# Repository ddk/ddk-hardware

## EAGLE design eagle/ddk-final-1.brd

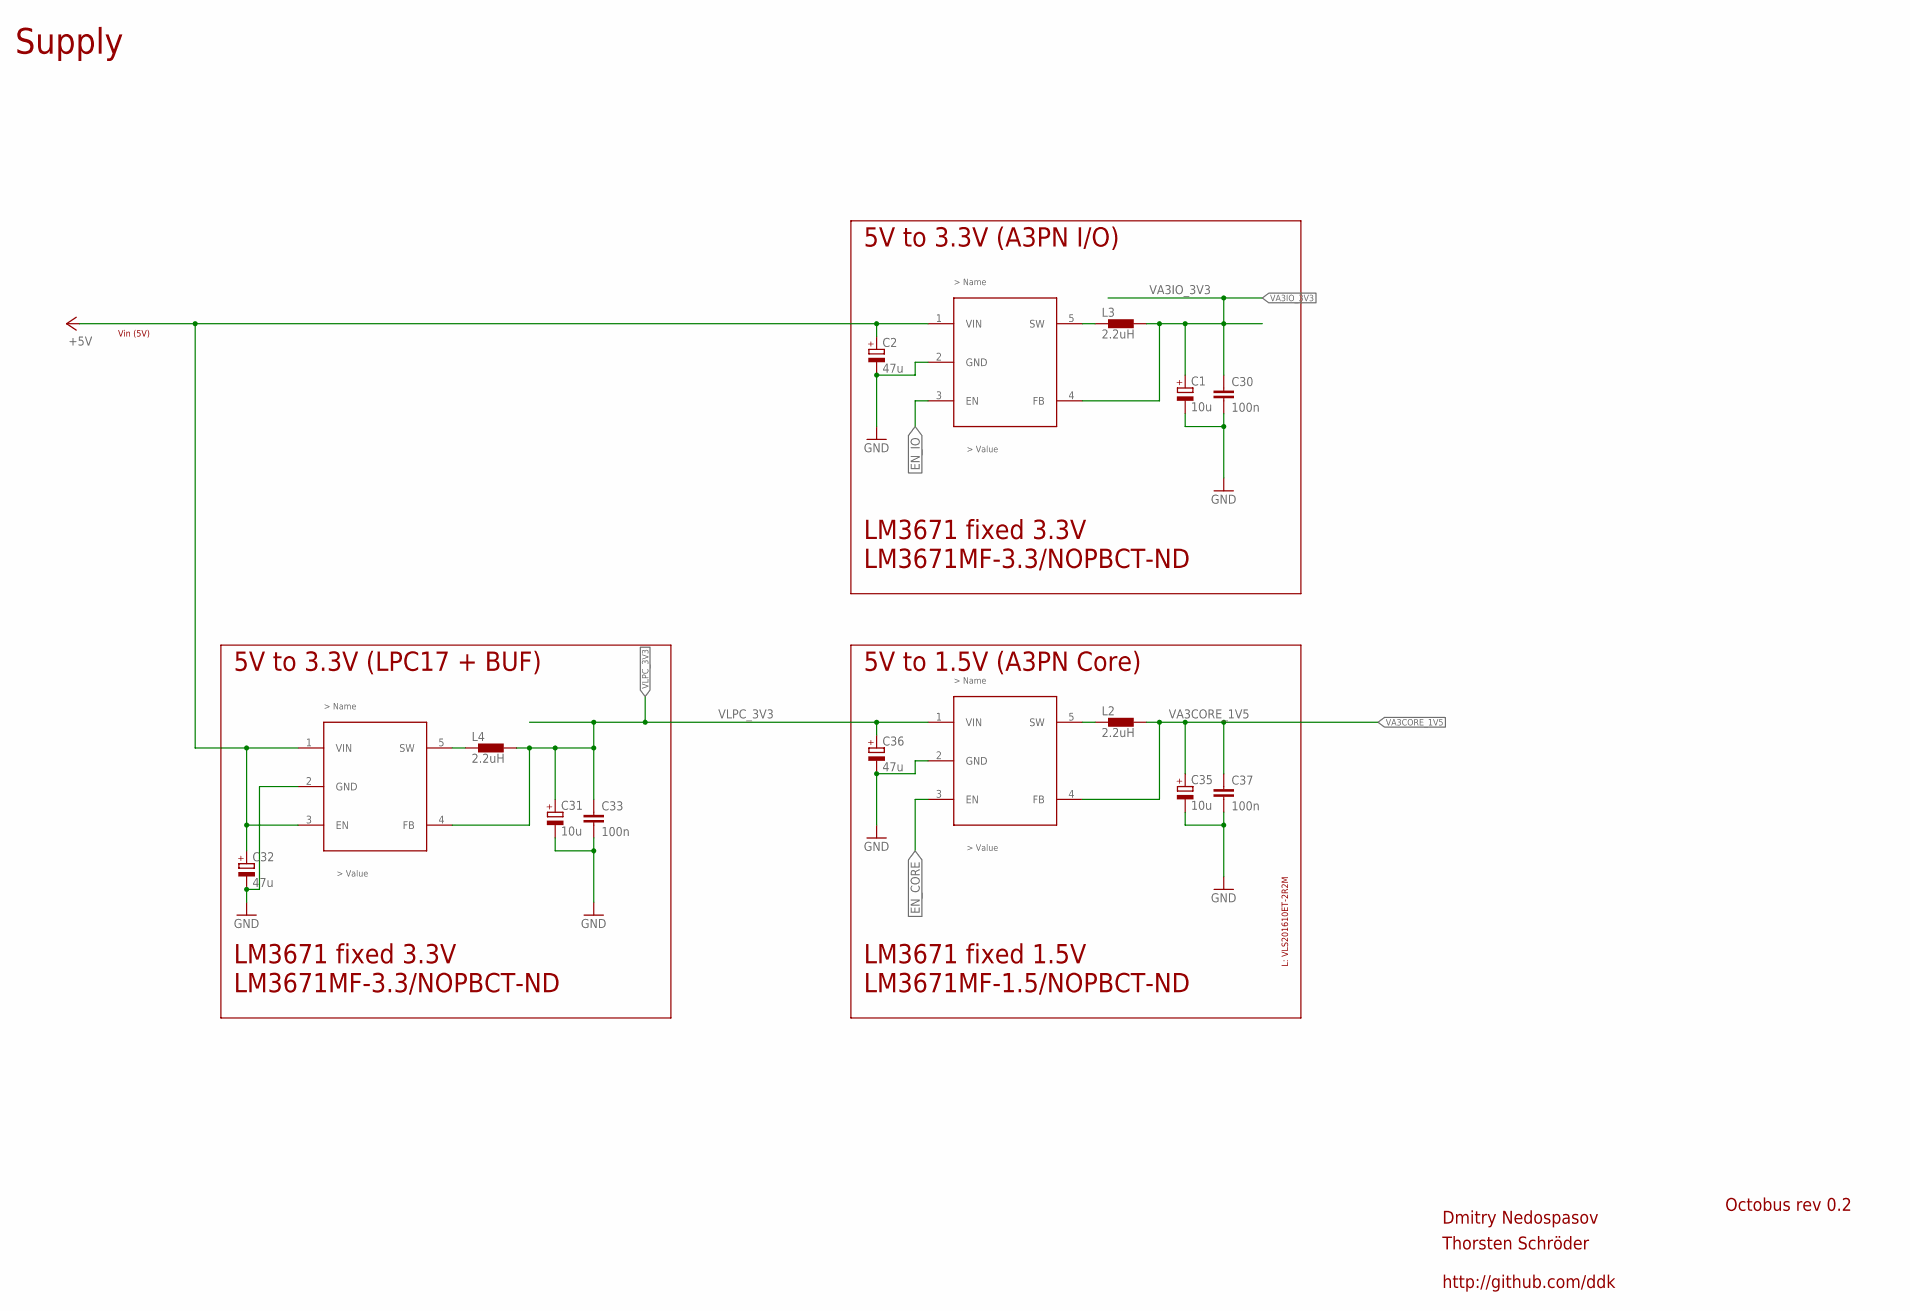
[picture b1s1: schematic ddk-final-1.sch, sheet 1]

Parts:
C1, C31, C35: 10u; CT3216
C2, C32, C36: 47u; CT3216
C30, C33, C37: 100n; C0603K
L2, L3, L4: 2.2uH; VLS_INDUCTOR
LM1: LM3671_3V3IO; SOT23-5L
LM2: LM3671_3V3_LPC; SOT23-5L
LM3671: LM3671_1V5; SOT23-5L

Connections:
+5V: C2.+, C32.+, LM1.1 (VIN), LM2.1 (VIN), LM2.3 (EN); also elsewhere on the board
EN_CORE: LM3671.3 (EN); also elsewhere on the board
EN_IO: LM1.3 (EN); also elsewhere on the board
GND: C1.-, C2.-, C30.2, C31.-, C32.-, C33.2, C35.-, C36.-, C37.2, LM1.2 (GND), LM2.2 (GND), LM3671.2 (GND); also elsewhere on the board
unnamed: L2.P$1 (1), LM3671.5 (SW)
unnamed: L3.P$1 (1), LM1.5 (SW)
unnamed: L4.P$1 (1), LM2.5 (SW)
VA3CORE_1V5: C35.+, C37.1, L2.P$2 (2), LM3671.4 (FB); also elsewhere on the board
VA3IO_3V3: C1.+, C30.1, L3.P$2 (2), LM1.4 (FB); also elsewhere on the board
VLPC_3V3: C31.+, C33.1, C36.+, L4.P$2 (2), LM2.4 (FB), LM3671.1 (VIN); also elsewhere on the board

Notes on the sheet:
Supply
Vin (5V)
5V to 1.5V (A3PN Core)
5V to 3.3V (A3PN I/O)
5V to 3.3V (LPC17 + BUF)
LM3671 fixed 1.5V LM3671MF-1.5/NOPBCT-ND
L: VLS201610ET-2R2M
LM3671 fixed 3.3V LM3671MF-3.3/NOPBCT-ND

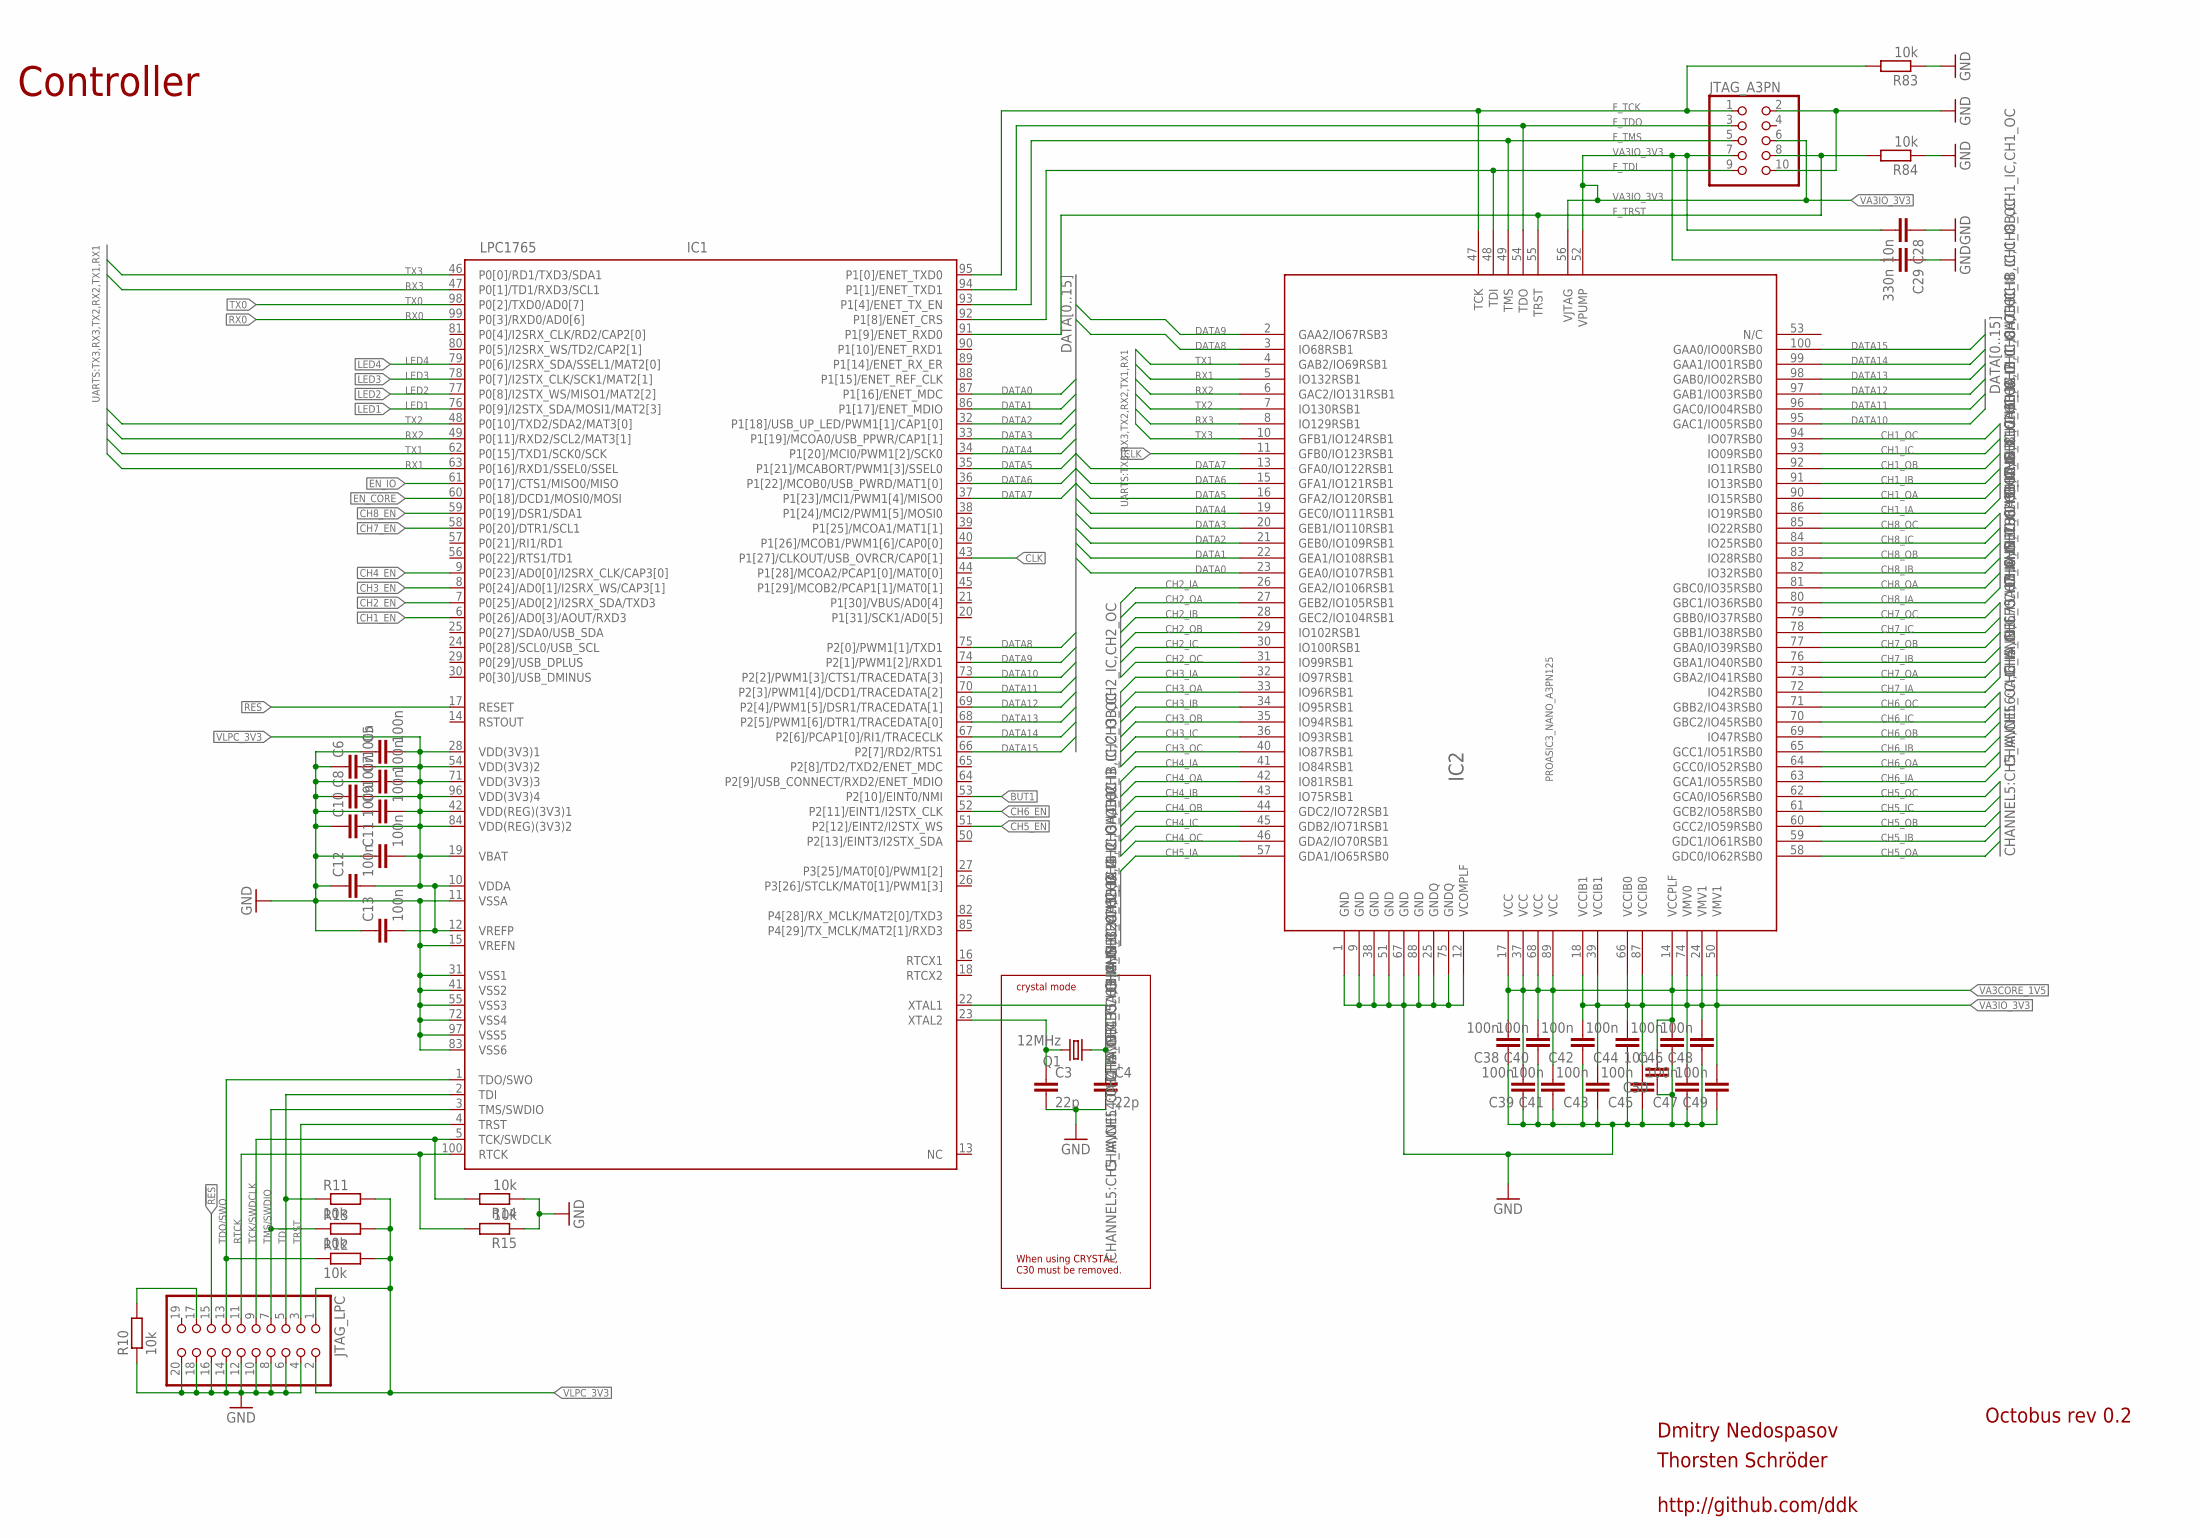
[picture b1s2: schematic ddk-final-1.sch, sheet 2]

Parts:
C3, C4: 22p; C0603K
C5, C6, C7, C8, C9, C10, C11, C12, C13, C38, C39, C40, C41, C42, C43, C44, C45, C46, C47, C48, C49: 100n; C0603K
C28, C50: 10n; C0603K
C29: 330n; C0603K
IC1: LPC1765; LQFP100-14X14
IC2: PROASIC3_NANO_A3PN125; VQFP100
JTAG_A3PN: PINHD-2X05_2.54-SMD; 2X05SMD
JTAG_LPC: PINHD-2X10_2.54-SMD; 2X10SMD
Q1: 12MHz; CTS406
R10, R11, R12, R13, R14, R15, R83, R84: 10k; R0603

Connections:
!RES!: IC1.17 (RESET), JTAG_LPC.15; also elsewhere on the board
BUT1: IC1.53 (P2[10]/EINT0/NMI); also elsewhere on the board
CH1_EN: IC1.6 (P0[26]/AD0[3]/AOUT/RXD3); also elsewhere on the board
CH1_IA: IC2.86 (IO19RSB0); also elsewhere on the board
CH1_IB: IC2.91 (IO13RSB0); also elsewhere on the board
CH1_IC: IC2.93 (IO09RSB0); also elsewhere on the board
CH1_OA: IC2.90 (IO15RSB0); also elsewhere on the board
CH1_OB: IC2.92 (IO11RSB0); also elsewhere on the board
CH1_OC: IC2.94 (IO07RSB0); also elsewhere on the board
CH2_EN: IC1.7 (P0[25]/AD0[2]/I2SRX_SDA/TXD3); also elsewhere on the board
CH2_IA: IC2.26 (GEA2/IO106RSB1); also elsewhere on the board
CH2_IB: IC2.28 (GEC2/IO104RSB1); also elsewhere on the board
CH2_IC: IC2.30 (IO100RSB1); also elsewhere on the board
CH2_OA: IC2.27 (GEB2/IO105RSB1); also elsewhere on the board
CH2_OB: IC2.29 (IO102RSB1); also elsewhere on the board
CH2_OC: IC2.31 (IO99RSB1); also elsewhere on the board
CH3_EN: IC1.8 (P0[24]/AD0[1]/I2SRX_WS/CAP3[1]); also elsewhere on the board
CH3_IA: IC2.32 (IO97RSB1); also elsewhere on the board
CH3_IB: IC2.34 (IO95RSB1); also elsewhere on the board
CH3_IC: IC2.36 (IO93RSB1); also elsewhere on the board
CH3_OA: IC2.33 (IO96RSB1); also elsewhere on the board
CH3_OB: IC2.35 (IO94RSB1); also elsewhere on the board
CH3_OC: IC2.40 (IO87RSB1); also elsewhere on the board
CH4_EN: IC1.9 (P0[23]/AD0[0]/I2SRX_CLK/CAP3[0]); also elsewhere on the board
CH4_IA: IC2.41 (IO84RSB1); also elsewhere on the board
CH4_IB: IC2.43 (IO75RSB1); also elsewhere on the board
CH4_IC: IC2.45 (GDB2/IO71RSB1); also elsewhere on the board
CH4_OA: IC2.42 (IO81RSB1); also elsewhere on the board
CH4_OB: IC2.44 (GDC2/IO72RSB1); also elsewhere on the board
CH4_OC: IC2.46 (GDA2/IO70RSB1); also elsewhere on the board
CH5_EN: IC1.51 (P2[12]/EINT2/I2STX_WS); also elsewhere on the board
CH5_IA: IC2.57 (GDA1/IO65RSB0); also elsewhere on the board
CH5_IB: IC2.59 (GDC1/IO61RSB0); also elsewhere on the board
CH5_IC: IC2.61 (GCB2/IO58RSB0); also elsewhere on the board
CH5_OA: IC2.58 (GDC0/IO62RSB0); also elsewhere on the board
CH5_OB: IC2.60 (GCC2/IO59RSB0); also elsewhere on the board
CH5_OC: IC2.62 (GCA0/IO56RSB0); also elsewhere on the board
CH6_EN: IC1.52 (P2[11]/EINT1/I2STX_CLK); also elsewhere on the board
CH6_IA: IC2.63 (GCA1/IO55RSB0); also elsewhere on the board
CH6_IB: IC2.65 (GCC1/IO51RSB0); also elsewhere on the board
CH6_IC: IC2.70 (GBC2/IO45RSB0); also elsewhere on the board
CH6_OA: IC2.64 (GCC0/IO52RSB0); also elsewhere on the board
CH6_OB: IC2.69 (IO47RSB0); also elsewhere on the board
CH6_OC: IC2.71 (GBB2/IO43RSB0); also elsewhere on the board
CH7_EN: IC1.58 (P0[20]/DTR1/SCL1); also elsewhere on the board
CH7_IA: IC2.72 (IO42RSB0); also elsewhere on the board
CH7_IB: IC2.76 (GBA1/IO40RSB0); also elsewhere on the board
CH7_IC: IC2.78 (GBB1/IO38RSB0); also elsewhere on the board
CH7_OA: IC2.73 (GBA2/IO41RSB0); also elsewhere on the board
CH7_OB: IC2.77 (GBA0/IO39RSB0); also elsewhere on the board
CH7_OC: IC2.79 (GBB0/IO37RSB0); also elsewhere on the board
CH8_EN: IC1.59 (P0[19]/DSR1/SDA1); also elsewhere on the board
CH8_IA: IC2.80 (GBC1/IO36RSB0); also elsewhere on the board
CH8_IB: IC2.82 (IO32RSB0); also elsewhere on the board
CH8_IC: IC2.84 (IO25RSB0); also elsewhere on the board
CH8_OA: IC2.81 (GBC0/IO35RSB0); also elsewhere on the board
CH8_OB: IC2.83 (IO28RSB0); also elsewhere on the board
CH8_OC: IC2.85 (IO22RSB0); also elsewhere on the board
CLK: IC1.43 (P1[27]/CLKOUT/USB_OVRCR/CAP0[1]), IC2.11 (GFB0/IO123RSB1); also elsewhere on the board
DATA0: IC1.87 (P1[16]/ENET_MDC), IC2.23 (GEA0/IO107RSB1)
DATA1: IC1.86 (P1[17]/ENET_MDIO), IC2.22 (GEA1/IO108RSB1)
DATA2: IC1.32 (P1[18]/USB_UP_LED/PWM1[1]/CAP1[0]), IC2.21 (GEB0/IO109RSB1)
DATA3: IC1.33 (P1[19]/MCOA0/USB_PPWR/CAP1[1]), IC2.20 (GEB1/IO110RSB1)
DATA4: IC1.34 (P1[20]/MCI0/PWM1[2]/SCK0), IC2.19 (GEC0/IO111RSB1)
DATA5: IC1.35 (P1[21]/MCABORT/PWM1[3]/SSEL0), IC2.16 (GFA2/IO120RSB1)
DATA6: IC1.36 (P1[22]/MCOB0/USB_PWRD/MAT1[0]), IC2.15 (GFA1/IO121RSB1)
DATA7: IC1.37 (P1[23]/MCI1/PWM1[4]/MISO0), IC2.13 (GFA0/IO122RSB1)
DATA8: IC1.75 (P2[0]/PWM1[1]/TXD1), IC2.3 (IO68RSB1)
DATA9: IC1.74 (P2[1]/PWM1[2]/RXD1), IC2.2 (GAA2/IO67RSB3)
DATA10: IC1.73 (P2[2]/PWM1[3]/CTS1/TRACEDATA[3]), IC2.95 (GAC1/IO05RSB0)
DATA11: IC1.70 (P2[3]/PWM1[4]/DCD1/TRACEDATA[2]), IC2.96 (GAC0/IO04RSB0)
DATA12: IC1.69 (P2[4]/PWM1[5]/DSR1/TRACEDATA[1]), IC2.97 (GAB1/IO03RSB0)
DATA13: IC1.68 (P2[5]/PWM1[6]/DTR1/TRACEDATA[0]), IC2.98 (GAB0/IO02RSB0)
DATA14: IC1.67 (P2[6]/PCAP1[0]/RI1/TRACECLK), IC2.99 (GAA1/IO01RSB0)
DATA15: IC1.66 (P2[7]/RD2/RTS1), IC2.100 (GAA0/IO00RSB0)
EN_CORE: IC1.60 (P0[18]/DCD1/MOSI0/MOSI); also elsewhere on the board
EN_IO: IC1.61 (P0[17]/CTS1/MISO0/MISO); also elsewhere on the board
F_TCK: IC1.95 (P1[0]/ENET_TXD0), IC2.47 (TCK), JTAG_A3PN.1, R83.2
F_TDI: IC1.92 (P1[8]/ENET_CRS), IC2.48 (TDI), JTAG_A3PN.9
F_TDO: IC1.94 (P1[1]/ENET_TXD1), IC2.54 (TDO), JTAG_A3PN.3
F_TMS: IC1.93 (P1[4]/ENET_TX_EN), IC2.49 (TMS), JTAG_A3PN.5
F_TRST: IC1.91 (P1[9]/ENET_RXD0), IC2.55 (TRST), JTAG_A3PN.8, R84.2
GND: C3.2, C4.2, C5.1, C6.1, C7.1, C8.1, C9.1, C10.1, C11.1, C12.1, C13.1, C28.1, C29.1, C38.1, C39.1, C40.1, C41.1, C42.1, C43.1, C44.1, C45.1, C46.1, C47.1, C48.1, C49.1, C50.1, IC1.11 (VSSA), IC1.15 (VREFN), IC1.31 (VSS1), IC1.41 (VSS2), IC1.55 (VSS3), IC1.72 (VSS4), IC1.83 (VSS6), IC1.97 (VSS5), IC2.1 (GND), IC2.9 (GND), IC2.12 (VCOMPLF), IC2.25 (GNDQ), IC2.38 (GND), IC2.51 (GND), IC2.67 (GND), IC2.75 (GNDQ), IC2.88 (GND), JTAG_A3PN.2, JTAG_A3PN.10, JTAG_LPC.4, JTAG_LPC.6, JTAG_LPC.8, JTAG_LPC.10, JTAG_LPC.12, JTAG_LPC.14, JTAG_LPC.16, JTAG_LPC.18, JTAG_LPC.20, R10.1, R14.1, R15.1, R83.1, R84.1; also elsewhere on the board
LED1: IC1.76 (P0[9]/I2STX_SDA/MOSI1/MAT2[3]); also elsewhere on the board
LED2: IC1.77 (P0[8]/I2STX_WS/MISO1/MAT2[2]); also elsewhere on the board
LED3: IC1.78 (P0[7]/I2STX_CLK/SCK1/MAT2[1]); also elsewhere on the board
LED4: IC1.79 (P0[6]/I2SRX_SDA/SSEL1/MAT2[0]); also elsewhere on the board
unnamed: JTAG_LPC.17, R10.2
unnamed: C4.1, IC1.22 (XTAL1), Q1.1
unnamed: C3.1, IC1.23 (XTAL2), Q1.3 (2)
RTCK: IC1.100 (RTCK), JTAG_LPC.11, R15.2
RX0: IC1.99 (P0[3]/RXD0/AD0[6]); also elsewhere on the board
RX1: IC1.63 (P0[16]/RXD1/SSEL0/SSEL), IC2.5 (IO132RSB1)
RX2: IC1.49 (P0[11]/RXD2/SCL2/MAT3[1]), IC2.6 (GAC2/IO131RSB1)
RX3: IC1.47 (P0[1]/TD1/RXD3/SCL1), IC2.8 (IO129RSB1)
TCK/SWDCLK: IC1.5 (TCK/SWDCLK), JTAG_LPC.9, R14.2
TDI: IC1.2 (TDI), JTAG_LPC.5, R11.1
TDO/SWO: IC1.1 (TDO/SWO), JTAG_LPC.13, R12.1
TMS/SWDIO: IC1.3 (TMS/SWDIO), JTAG_LPC.7, R13.1
TRST: IC1.4 (TRST), JTAG_LPC.3
TX0: IC1.98 (P0[2]/TXD0/AD0[7]); also elsewhere on the board
TX1: IC1.62 (P0[15]/TXD1/SCK0/SCK), IC2.4 (GAB2/IO69RSB1)
TX2: IC1.48 (P0[10]/TXD2/SDA2/MAT3[0]), IC2.7 (IO130RSB1)
TX3: IC1.46 (P0[0]/RD1/TXD3/SDA1), IC2.10 (GFB1/IO124RSB1)
VA3CORE_1V5: C38.2, C39.2, C40.2, C41.2, C46.2, C50.2, IC2.14 (VCCPLF), IC2.17 (VCC), IC2.37 (VCC), IC2.68 (VCC), IC2.89 (VCC); also elsewhere on the board
VA3IO_3V3: C28.2, C29.2, C42.2, C43.2, C44.2, C45.2, C47.2, C48.2, C49.2, IC2.18 (VCCIB1), IC2.24 (VMV1), IC2.39 (VCCIB1), IC2.50 (VMV1), IC2.52 (VPUMP), IC2.56 (VJTAG), IC2.66 (VCCIB0), IC2.74 (VMV0), IC2.87 (VCCIB0), JTAG_A3PN.6, JTAG_A3PN.7; also elsewhere on the board
VLPC_3V3: C5.2, C6.2, C7.2, C8.2, C9.2, C10.2, C11.2, C12.2, C13.2, IC1.10 (VDDA), IC1.12 (VREFP), IC1.19 (VBAT), IC1.28 (VDD(3V3)1), IC1.42 (VDD(REG)(3V3)1), IC1.54 (VDD(3V3)2), IC1.71 (VDD(3V3)3), IC1.84 (VDD(REG)(3V3)2), IC1.96 (VDD(3V3)4), JTAG_LPC.1, JTAG_LPC.2, R11.2, R12.2, R13.2; also elsewhere on the board

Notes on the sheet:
Controller
When using CRYSTAL, C30 must be removed.
crystal mode

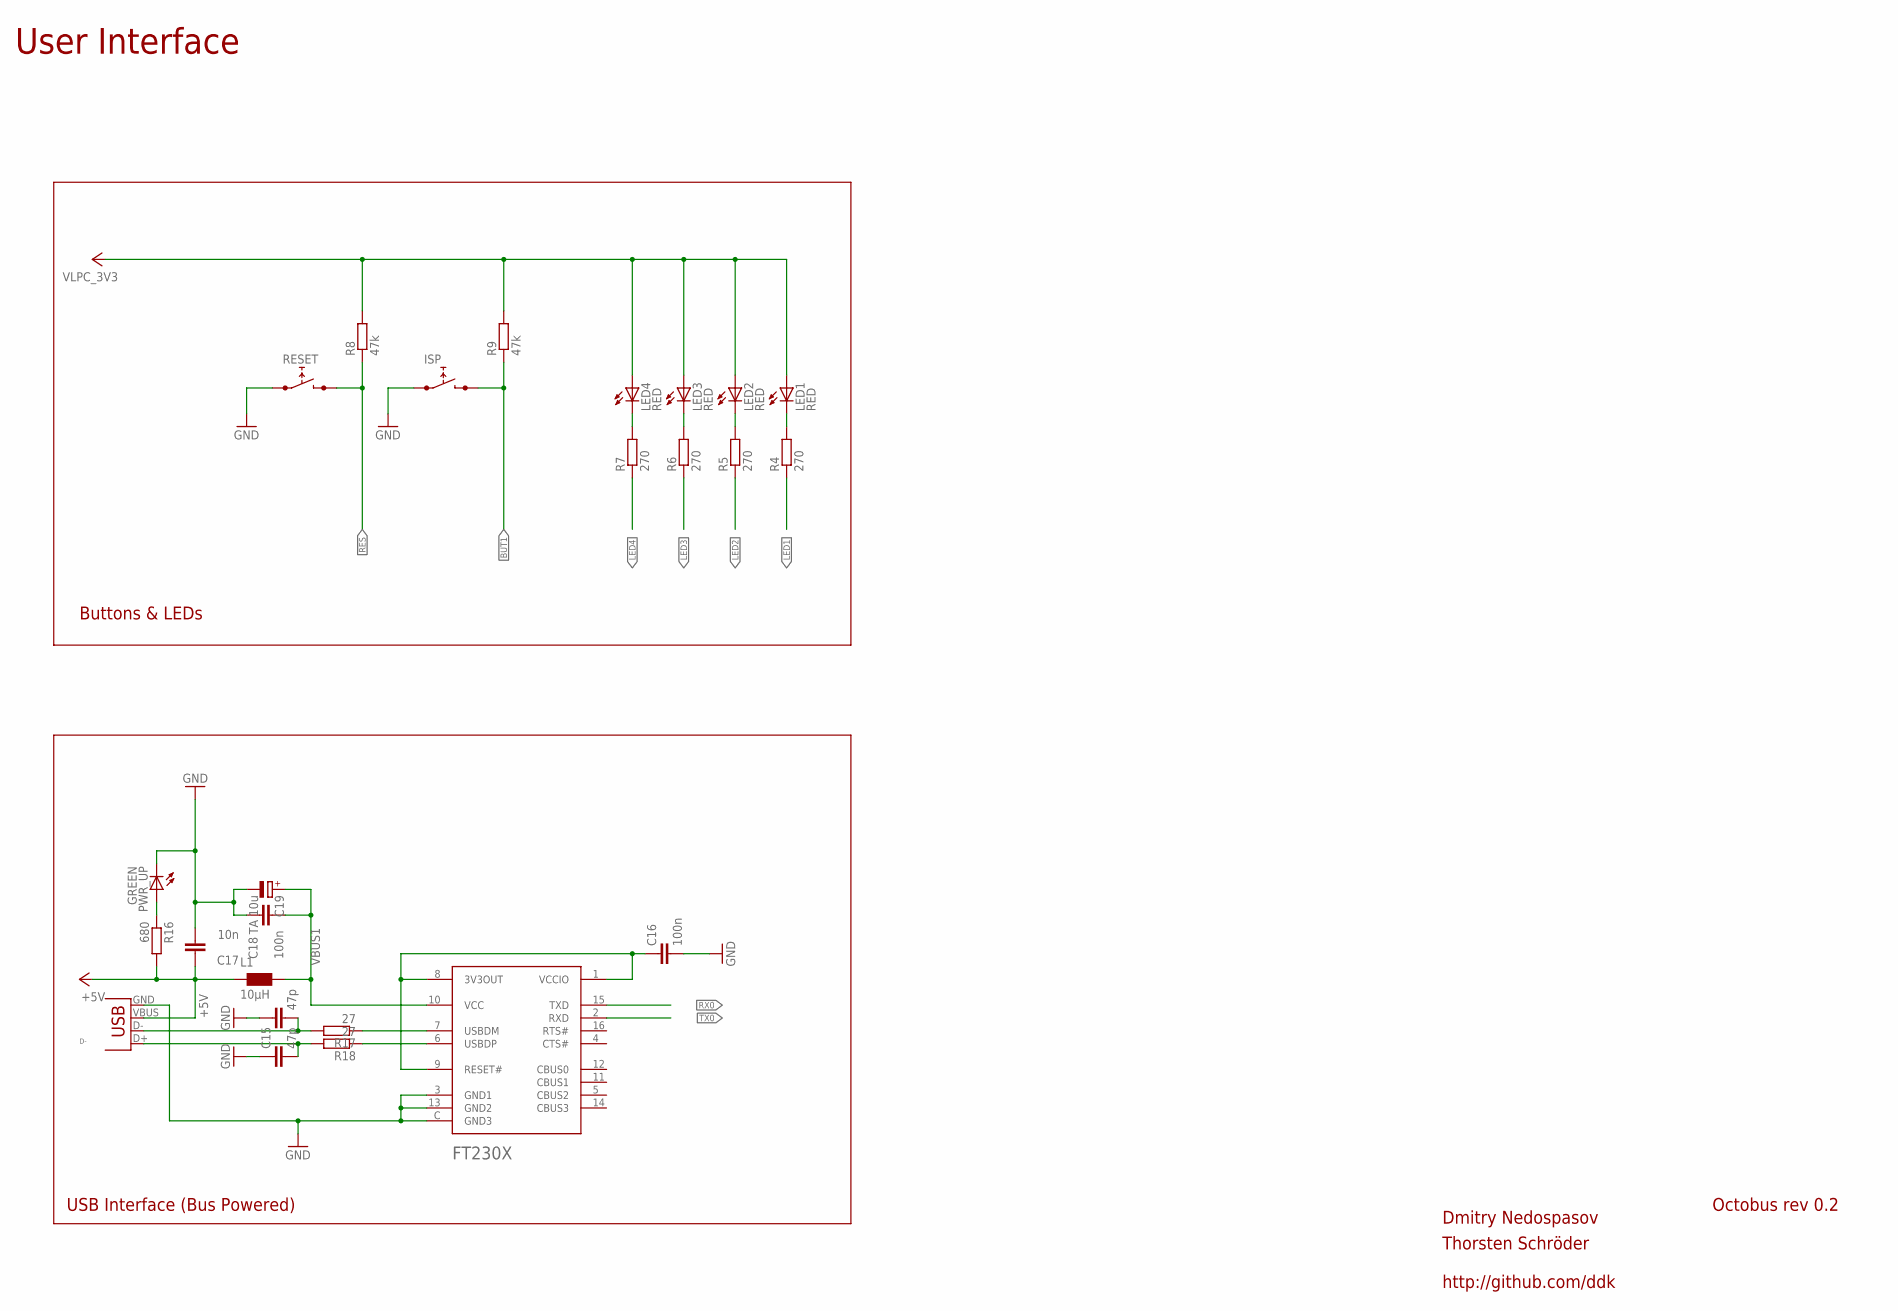
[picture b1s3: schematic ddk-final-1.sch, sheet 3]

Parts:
C14, C15: 47p; C0603
C16, C18: 100n; C0603
C17: 10n; C0603
C19: TA 10u; CT3216
FT230X: SERIAL_FT230XQ; SERIAL_QFN4X4-16
ISP: B3U-1000P
L1: 10µH; WE-KI_0805_B
LED1, LED2, LED3, LED4: RED; CHIP-LED0603
PWR_UP: GREEN; CHIPLED_0603
R4, R5, R6, R7: 270; R0603
R8, R9: 47k; R0603
R16: 680; R0603
R17, R18: 27; R0603
RESET: B3U-1000P
X1: USBSMD; USB-MINIB

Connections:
!RES!: R8.1, RESET.P$2 (1); also elsewhere on the board
+5V: C17.2, L1.2 (1), R16.2, X1.VBUS; also elsewhere on the board
BUT1: ISP.P$2 (1), R9.1; also elsewhere on the board
D+: C14.1, R17.2, X1.D-
D-: C15.1, R18.2, X1.D+
GND: C14.2, C15.2, C16.1, C17.1, C18.2, C19.-, FT230X.3 (GND1), FT230X.13 (GND2), FT230X.C (GND3), ISP.P$1 (0), PWR_UP.C, RESET.P$1 (0), X1.GND; also elsewhere on the board
LED1: R4.1; also elsewhere on the board
LED2: R5.1; also elsewhere on the board
LED3: R6.1; also elsewhere on the board
LED4: R7.1; also elsewhere on the board
unnamed: FT230X.6 (USBDP), R18.1
unnamed: FT230X.7 (USBDM), R17.1
unnamed: LED4.C, R7.2
unnamed: LED3.C, R6.2
unnamed: LED2.C, R5.2
unnamed: LED1.C, R4.2
unnamed: C16.2, FT230X.1 (VCCIO), FT230X.8 (3V3OUT), FT230X.9 (RESET#)
unnamed: PWR_UP.A, R16.1
RX0: FT230X.15 (TXD); also elsewhere on the board
TX0: FT230X.2 (RXD); also elsewhere on the board
VBUS1: C18.1, C19.+, FT230X.10 (VCC), L1.1 (2)
VLPC_3V3: LED1.A, LED2.A, LED3.A, LED4.A, R8.2, R9.2; also elsewhere on the board

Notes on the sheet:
User Interface
Buttons & LEDs
USB Interface (Bus Powered)

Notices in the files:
eagle/ddk-final-1.brd:
(C) 2013
(C) 2013 Dmitry Nedospasov & Thorsten Schroeder
parts and their libraries:
devio: The Library is released under the terms of the Beer Ware License (Revision 42).
wuerth-elektronik: Copyright: Würth Elektronik eiSos
actel-proasic3: Copyright (C) 2013, Thorsten Schroeder  Germany, Berlin
This file will be published under a less restrictive opensource license.
